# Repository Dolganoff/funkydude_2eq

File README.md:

funkydude_2eq
=============

funky dude 2eq preamp

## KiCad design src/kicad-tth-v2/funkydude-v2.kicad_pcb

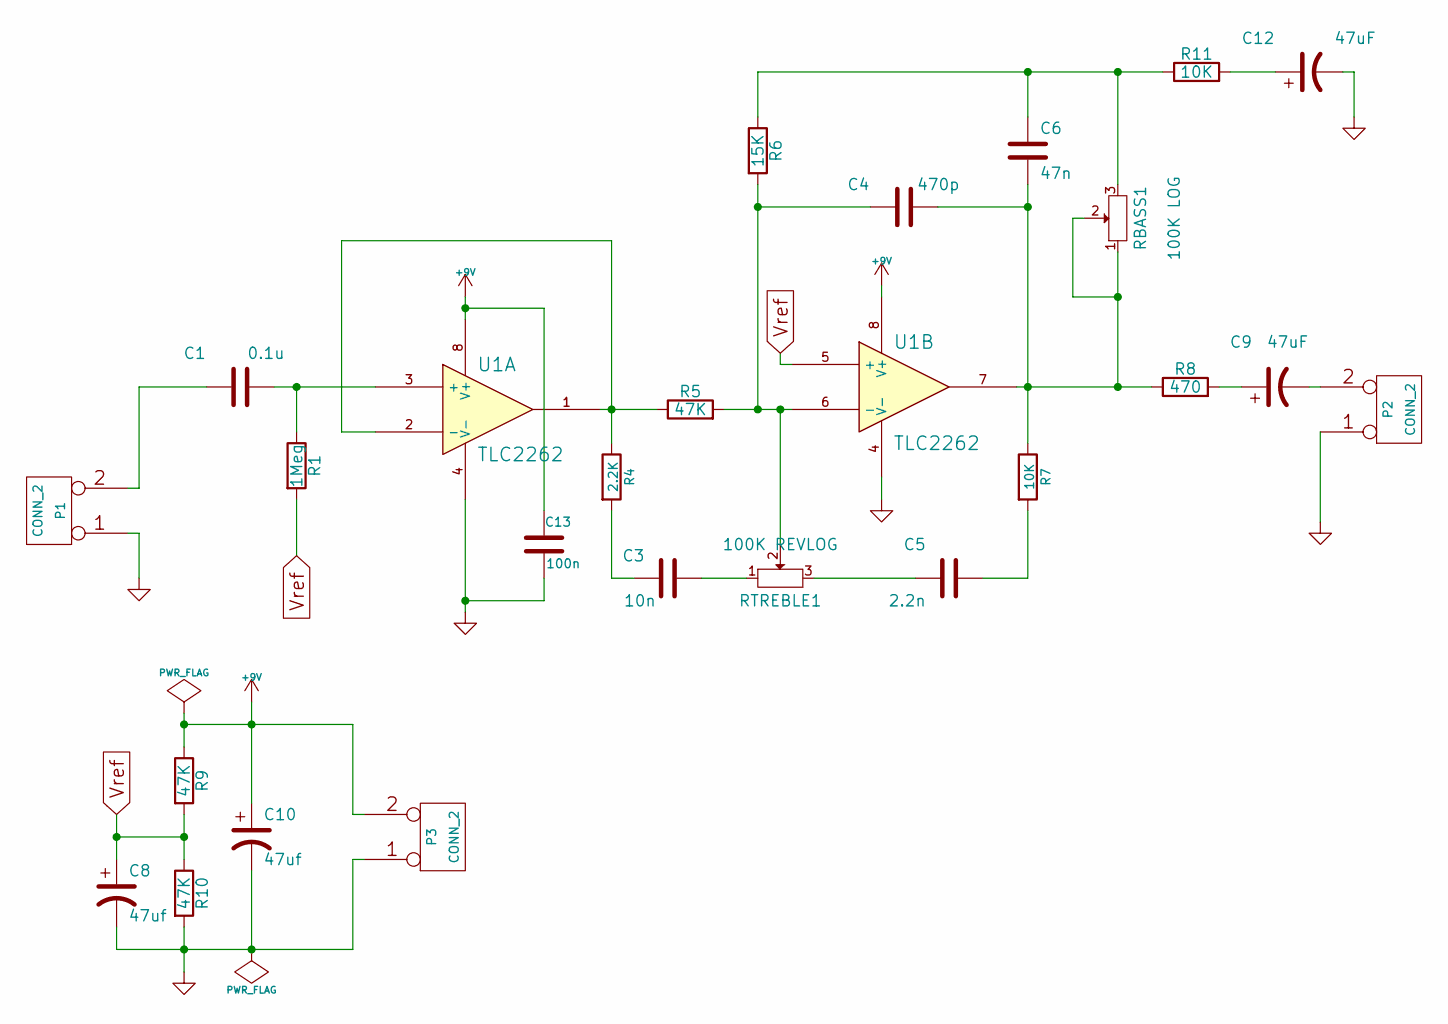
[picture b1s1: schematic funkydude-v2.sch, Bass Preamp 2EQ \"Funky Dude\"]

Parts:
C1: 0.1u; C2-LARGE_PADS
C3: 10n; C2-LARGE_PADS
C4: 470p; C2-LARGE_PADS
C5: 2.2n; C2-LARGE_PADS
C6: 47n; C2-LARGE_PADS
C8, C10: 47uf; C1V5-LARGE_PADS
C9, C12: 47uF; C1V5-LARGE_PADS
C13: 100n; C2-LARGE_PADS
P1, P2, P3: CONN_2; SIL-2-LARGE_PADS
R1: 1Meg; R3-LARGE_PADS
R4: 2.2K; R3-LARGE_PADS
R5, R9, R10: 47K; R3-LARGE_PADS
R6: 15K; R3-LARGE_PADS
R7, R11: 10K; R3-LARGE_PADS
R8: 470; R3-LARGE_PADS
RBASS1: 100K LOG; SIL-3-LARGE_PADS
RTREBLE1: 100K REVLOG; SIL-3-LARGE_PADS
U1: TLC2262; DIP-8_LARGE_PADS

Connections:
+9V: C10.1, C13.1, P3.2 (PM), R9.1, U1.8 (V+)
GND: C8.2, C10.2, C12.2, C13.2, P1.1, P2.1, P3.1, R10.2, U1.4 (V-)
unnamed: C1.1, P1.2 (PM)
unnamed: C1.2, R1.1, U1.3 (+)
unnamed: C3.1, R4.2
unnamed: C3.2, RTREBLE1.1
unnamed: C4.1, R5.2, R6.2, RTREBLE1.2, U1.6 (-)
unnamed: C4.2, C6.2, R7.1, R8.1, RBASS1.1, RBASS1.2, U1.7
unnamed: C5.1, RTREBLE1.3
unnamed: C5.2, R7.2
unnamed: C6.1, R6.1, R11.1, RBASS1.3
unnamed: C9.1, R8.2
unnamed: C9.2, P2.2 (PM)
unnamed: C12.1, R11.2
unnamed: R4.1, R5.1, U1.1, U1.2 (-)
Vref: C8.1, R1.2, R9.2, R10.1, U1.5 (+)

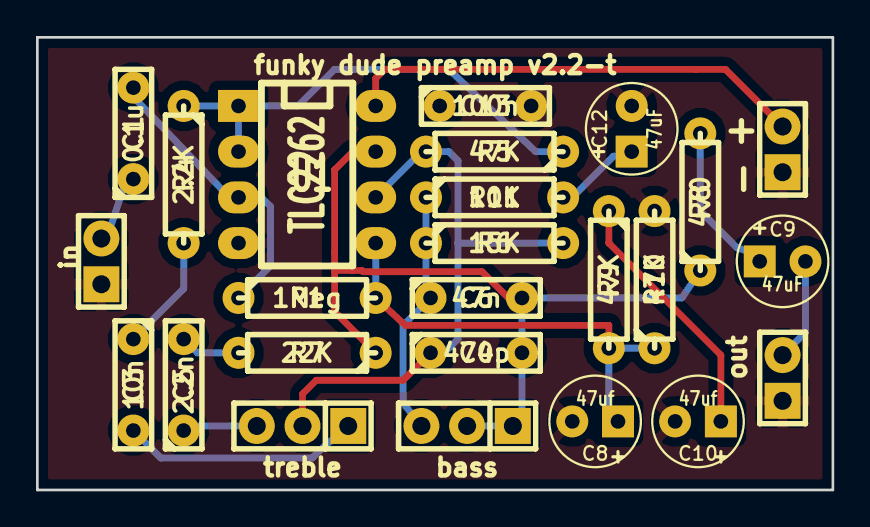
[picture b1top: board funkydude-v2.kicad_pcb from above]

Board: 2 copper layers, 44.2 x 25.1 mm, 25 parts (0 on the bottom side), 16 nets.

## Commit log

2014-08-08 license
2014-08-08 deleted license.bak
2014-08-24 separate smd and tth projects
2014-10-12 2014-10-12
2014-10-12 modified readme
2014-10-21 version_2.0 initial
2014-10-22 2014-10-22
2014-10-22 2014-10-23
2014-10-23 2014-10-23.2 - PCB is routed
2014-11-02 2014-11-02 pcb changes
2014-11-08 changed switch to smaller symbol
2014-11-09 change to TLC2262
2014-11-09 pcb changes
2014-11-10 smaller bcb design, removed gain trim
2014-11-10 added dimension drawing
2014-11-10 bump schematics date
2014-11-10 move old sims
2014-11-10 create simulation (freq. responce)
2014-11-30 adding pull-down resistors
2014-12-09 pull-down R deleted, new plot files
2015-04-04 test pos pnp file
2021-08-29 updated version

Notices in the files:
src/kicad-tth-v2/funkydude-v2.kicad_pcb:
Licenced under CERN OHL v1.2
src/kicad-tth-v2/funkydude-v2.sch:
Open Hardware, Licensed under CERN OHL v.1.2
